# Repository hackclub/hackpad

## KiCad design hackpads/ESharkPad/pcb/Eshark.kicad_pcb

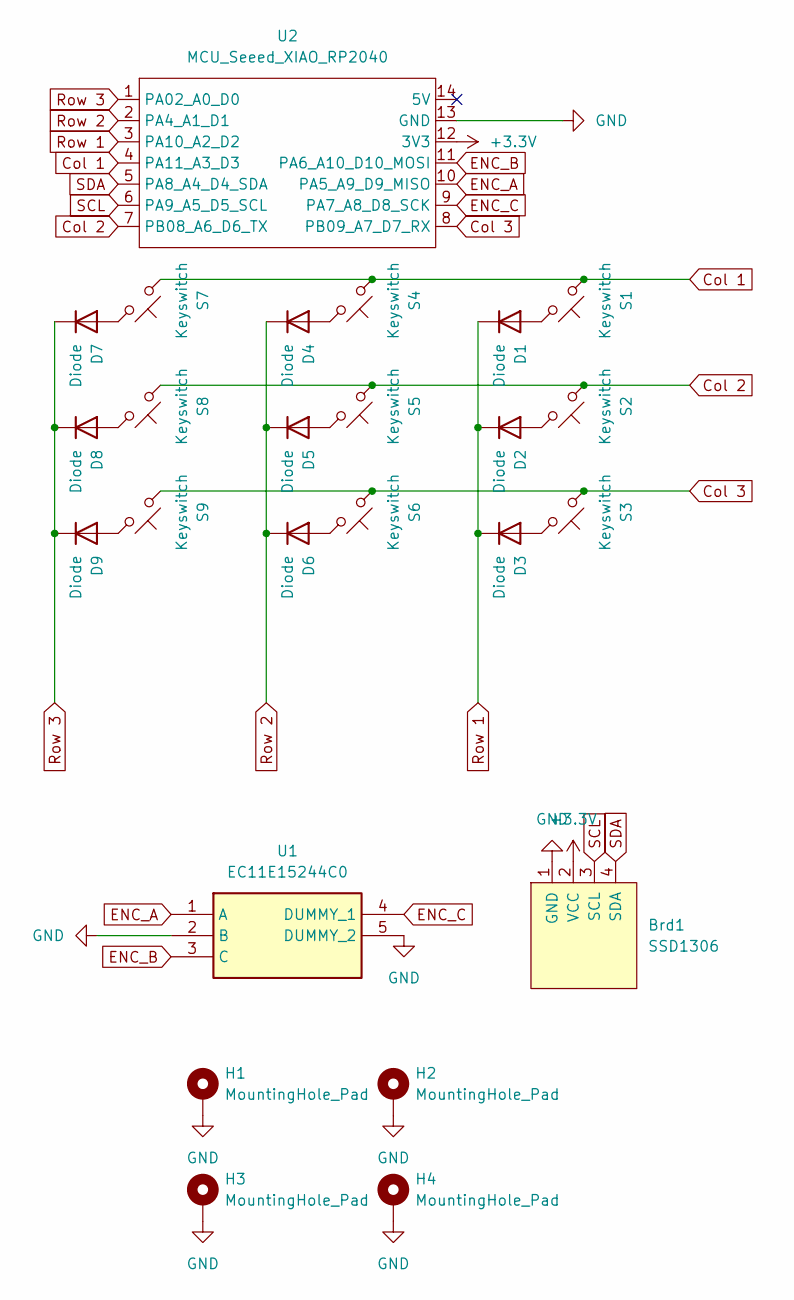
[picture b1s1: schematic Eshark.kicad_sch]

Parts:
Brd1: SSD1306; 128x64OLED
D1, D2, D3, D4, D5, D6, D7, D8, D9: Diode; Diode_DO-35
H1, H2, H3, H4: MountingHole_Pad; MountingHole_2.5mm_Pad_Via
S1, S2, S3, S4, S5, S6, S7, S8, S9: Keyswitch; Kailh-PG1353-Hotswap-1U
U1: EC11E15244C0; EC11B202440M; Manufacturer_Part_Number EC11E15244C0
U2: MCU_Seeed_XIAO_RP2040; Seeed_XIAO_RP2040

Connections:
+3.3V: Brd1.2 (VCC), U2.12 (3V3)
Col 1: S1.1, S4.1, S7.1, U2.4 (PA11_A3_D3)
Col 2: S2.1, S5.1, S8.1, U2.7 (PB08_A6_D6_TX)
Col 3: S3.1, S6.1, S9.1, U2.8 (PB09_A7_D7_RX)
ENC_A: U1.1 (A), U2.10 (PA5_A9_D9_MISO)
ENC_B: U1.3 (C), U2.11 (PA6_A10_D10_MOSI)
ENC_C: U1.4 (DUMMY_1), U2.9 (PA7_A8_D8_SCK)
GND: Brd1.1 (GND), H1.1, H2.1, H3.1, H4.1, U1.2 (B), U1.5 (DUMMY_2), U2.13 (GND)
unnamed: D1.2 (A), S1.2
unnamed: D2.2 (A), S2.2
unnamed: D3.2 (A), S3.2
unnamed: D4.2 (A), S4.2
unnamed: D5.2 (A), S5.2
unnamed: D6.2 (A), S6.2
unnamed: D7.2 (A), S7.2
unnamed: D8.2 (A), S8.2
unnamed: D9.2 (A), S9.2
Row 1: D1.1 (K), D2.1 (K), D3.1 (K), U2.3 (PA10_A2_D2)
Row 2: D4.1 (K), D5.1 (K), D6.1 (K), U2.2 (PA4_A1_D1)
Row 3: D7.1 (K), D8.1 (K), D9.1 (K), U2.1 (PA02_A0_D0)
SCL: Brd1.3 (SCL), U2.6 (PA9_A5_D5_SCL)
SDA: Brd1.4 (SDA), U2.5 (PA8_A4_D4_SDA)

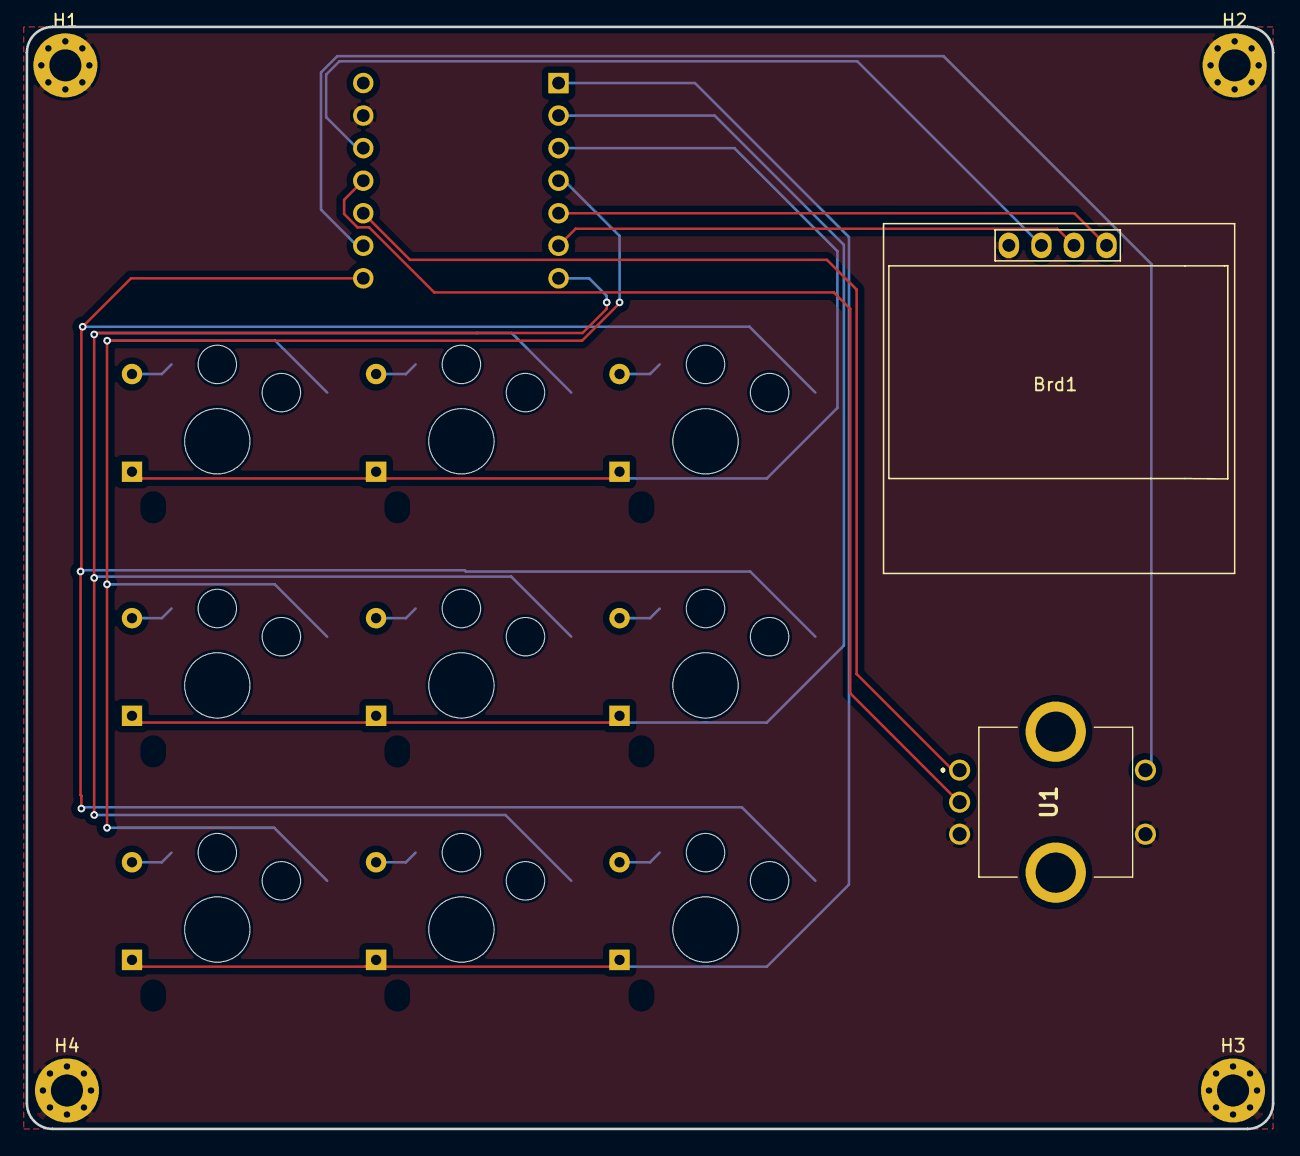
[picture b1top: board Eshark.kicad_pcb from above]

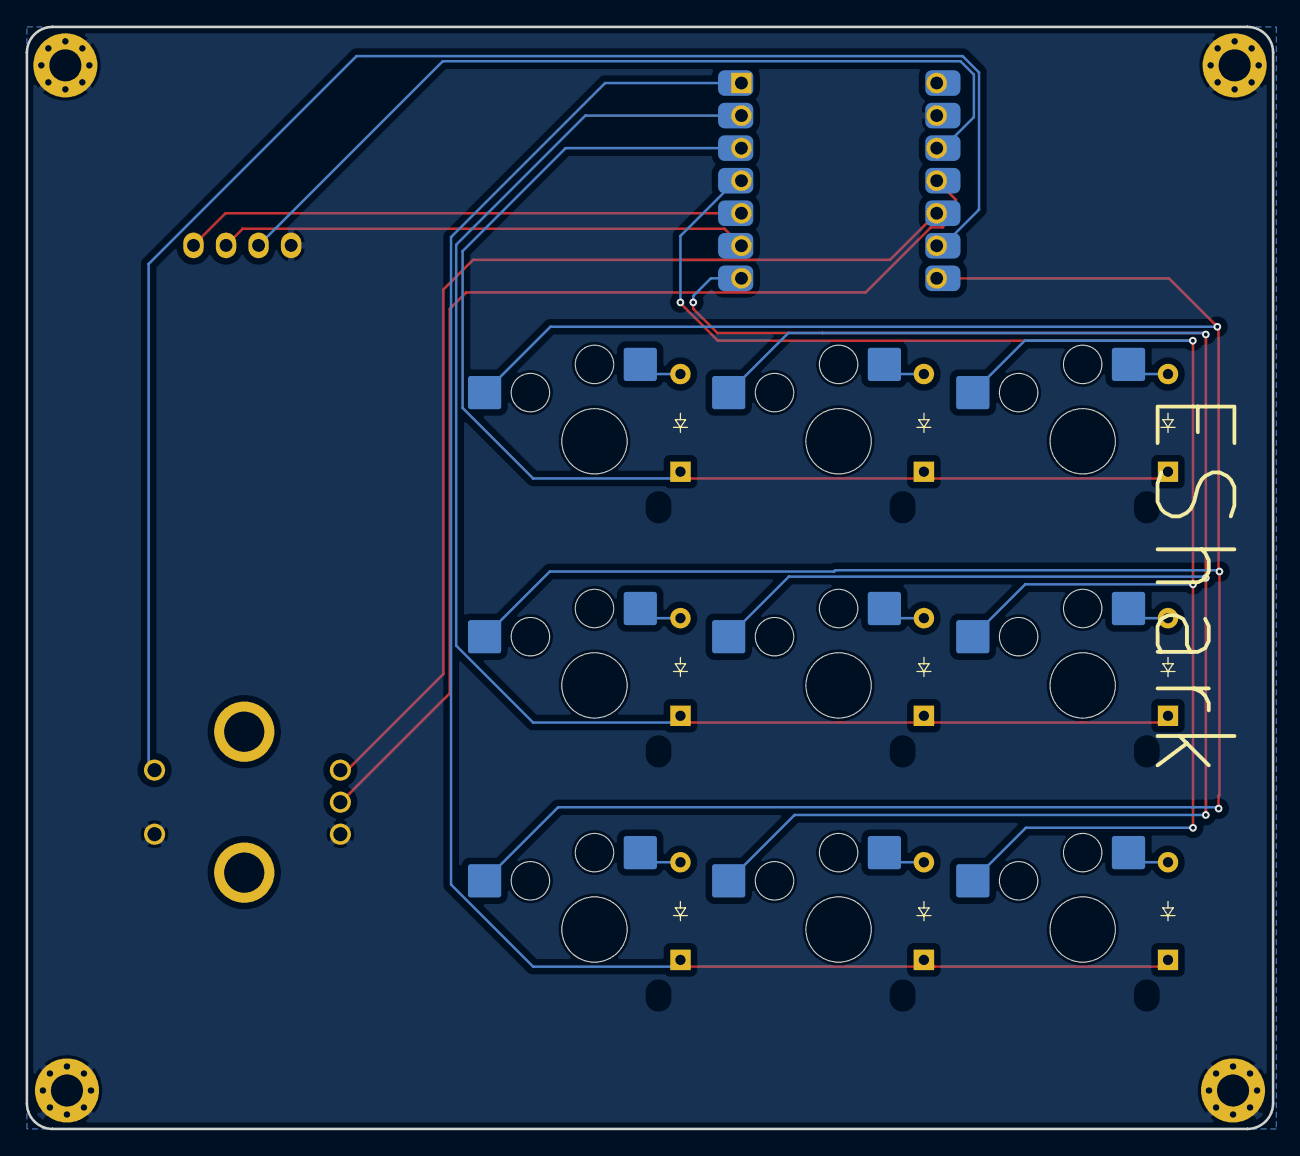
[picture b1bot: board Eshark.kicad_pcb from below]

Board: 2 copper layers, 97.2 x 86.0 mm, 25 parts (19 on the bottom side), 22 nets.

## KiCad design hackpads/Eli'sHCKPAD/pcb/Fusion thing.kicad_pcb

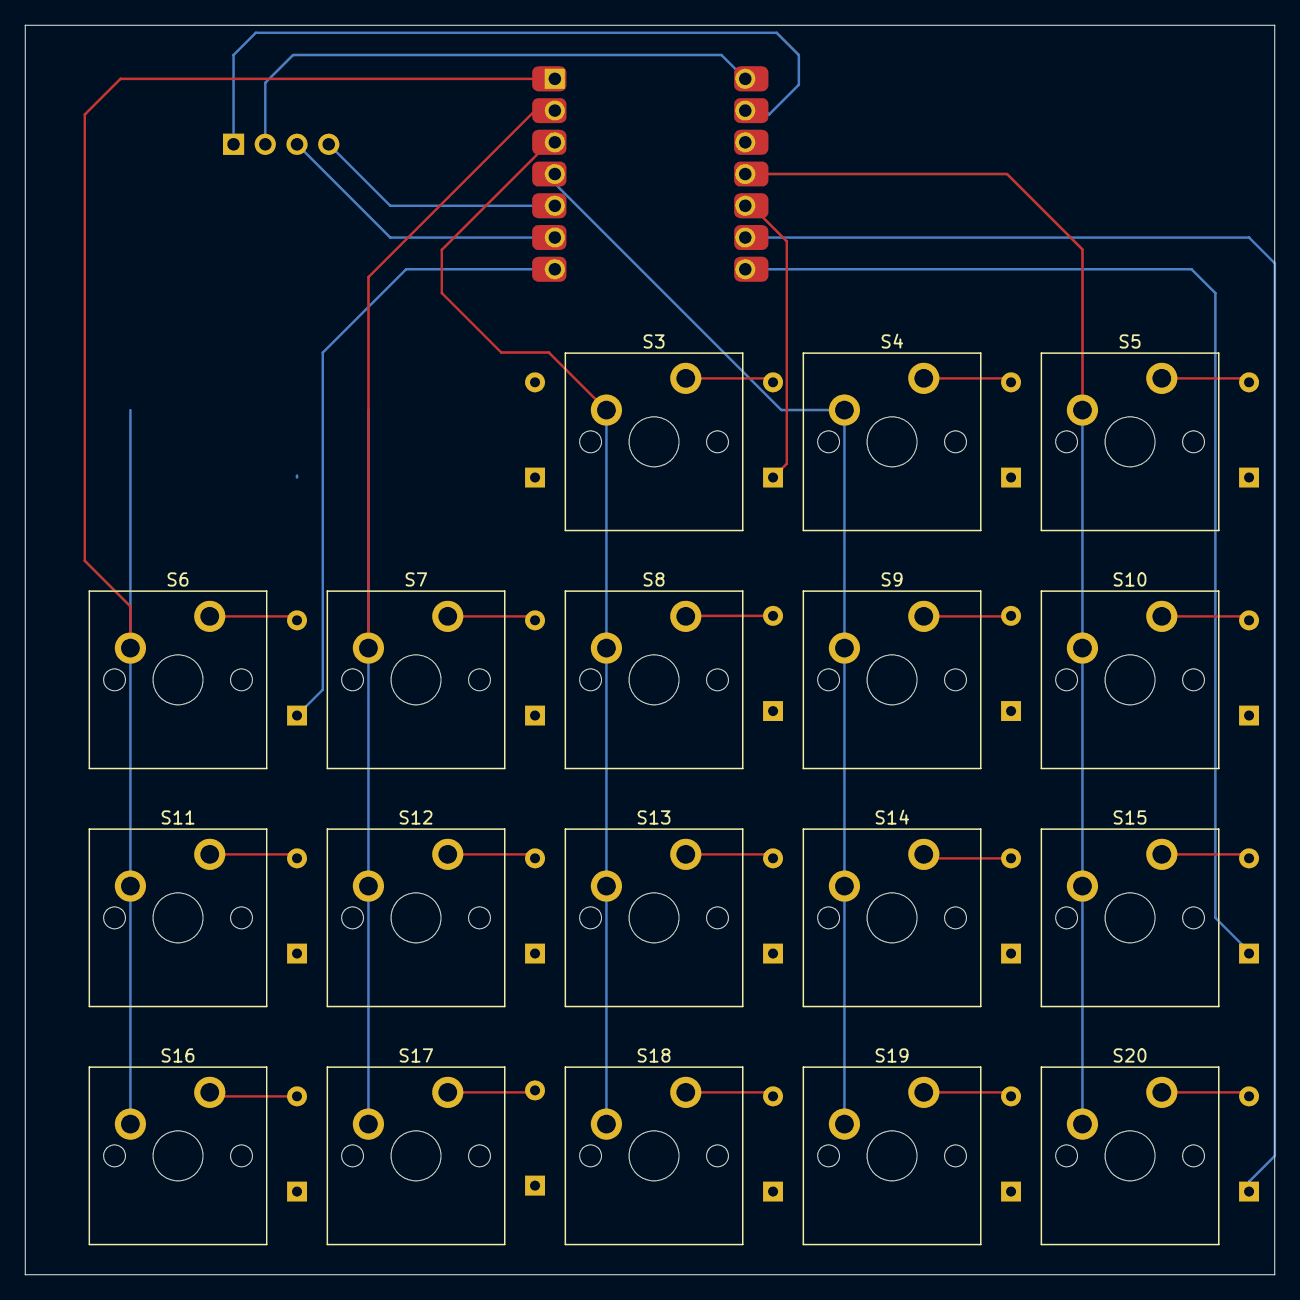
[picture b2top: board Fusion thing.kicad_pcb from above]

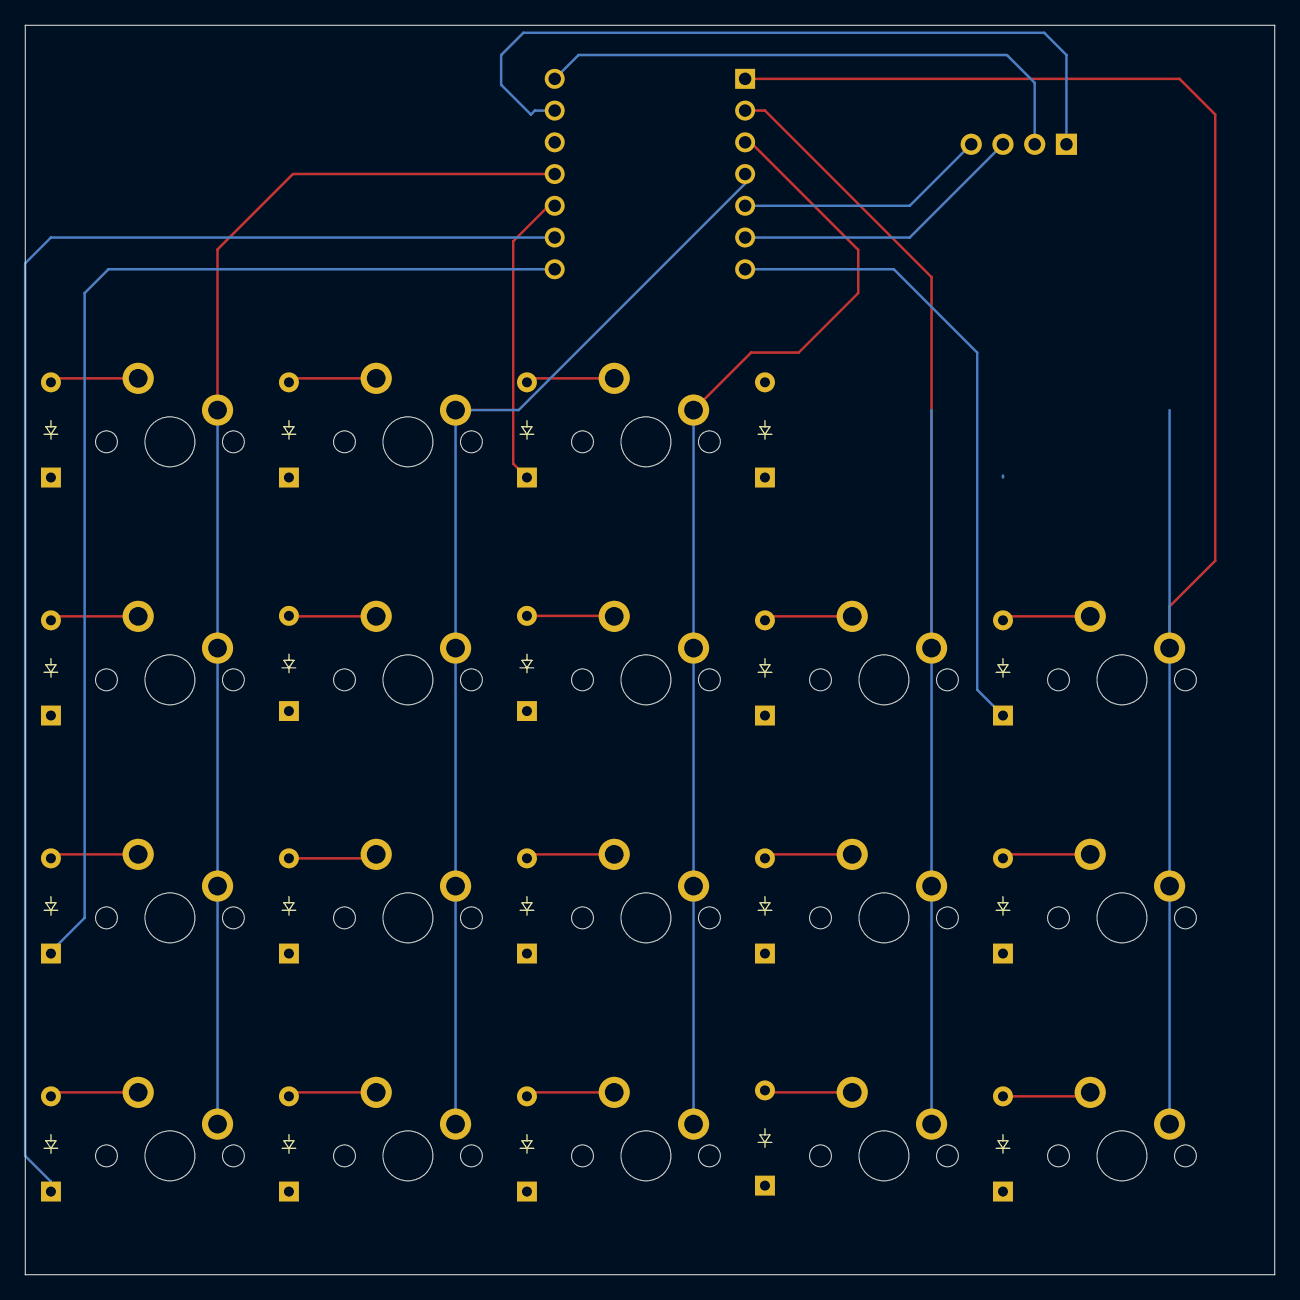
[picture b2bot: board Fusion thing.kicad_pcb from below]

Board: 2 copper layers, 100.0 x 100.0 mm, 39 parts (19 on the bottom side), 31 nets.

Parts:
D2, D3, D4, D5, D6, D7, D8, D9, D10, D11, D12, D13, D14, D15, D16, D17, D18, D19, D20: Diode; Diode_DO-35
J1: OLED_128x64
S3, S4, S5, S6, S7, S8, S9, S10, S11, S12, S13, S14, S15, S16, S17, S18, S19, S20: Keyswitch; MX_PCB_1.00u
U1: MCU_Seeed_XIAO_RP2040; Seeed_XIAO_RP2040

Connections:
Gnd: J1.1 (GND), U1.13 (GND)
unnamed: D3.2 (A), S3.2
unnamed: D4.2 (A), S4.2
unnamed: D5.2 (A), S5.2
unnamed: D6.2 (A), S6.2
unnamed: D7.2 (A), S7.2
unnamed: D8.2 (A), S8.2
unnamed: D9.2 (A), S9.2
unnamed: D10.2 (A), S10.2
unnamed: D11.2 (A), S11.2
unnamed: D12.2 (A), S12.2
unnamed: D13.2 (A), S13.2
unnamed: D14.2 (A), S14.2
unnamed: D15.2 (A), S15.2
unnamed: D16.2 (A), S16.2
unnamed: D17.2 (A), S17.2
unnamed: D18.2 (A), S18.2
unnamed: D19.2 (A), S19.2
unnamed: D20.2 (A), S20.2
SCL: J1.3 (SCL), U1.6 (PA9_A5_D5_SCL)
SDA: J1.4 (SDA), U1.5 (PA8_A4_D4_SDA)
VCC: J1.2 (VCC), U1.14 (5V)
column1: S6.1, S11.1, S16.1, U1.1 (PA02_A0_D0)
column2: S7.1, S12.1, S17.1, U1.2 (PA4_A1_D1)
column3: S3.1, S8.1, S13.1, S18.1, U1.3 (PA10_A2_D2)
column4: S4.1, S9.1, S14.1, S19.1, U1.4 (PA11_A3_D3)
column5: S5.1, S10.1, S15.1, S20.1, U1.11 (PA6_A10_D10_MOSI)
row1: D2.1 (K), D3.1 (K), D4.1 (K), D5.1 (K), U1.10 (PA5_A9_D9_MISO)
row2: D6.1 (K), D7.1 (K), D8.1 (K), D9.1 (K), D10.1 (K), U1.7 (PB08_A6_D6_TX)
row3: D11.1 (K), D12.1 (K), D13.1 (K), D14.1 (K), D15.1 (K), U1.8 (PB09_A7_D7_RX)
row4: D16.1 (K), D17.1 (K), D18.1 (K), D19.1 (K), D20.1 (K), U1.9 (PA7_A8_D8_SCK)

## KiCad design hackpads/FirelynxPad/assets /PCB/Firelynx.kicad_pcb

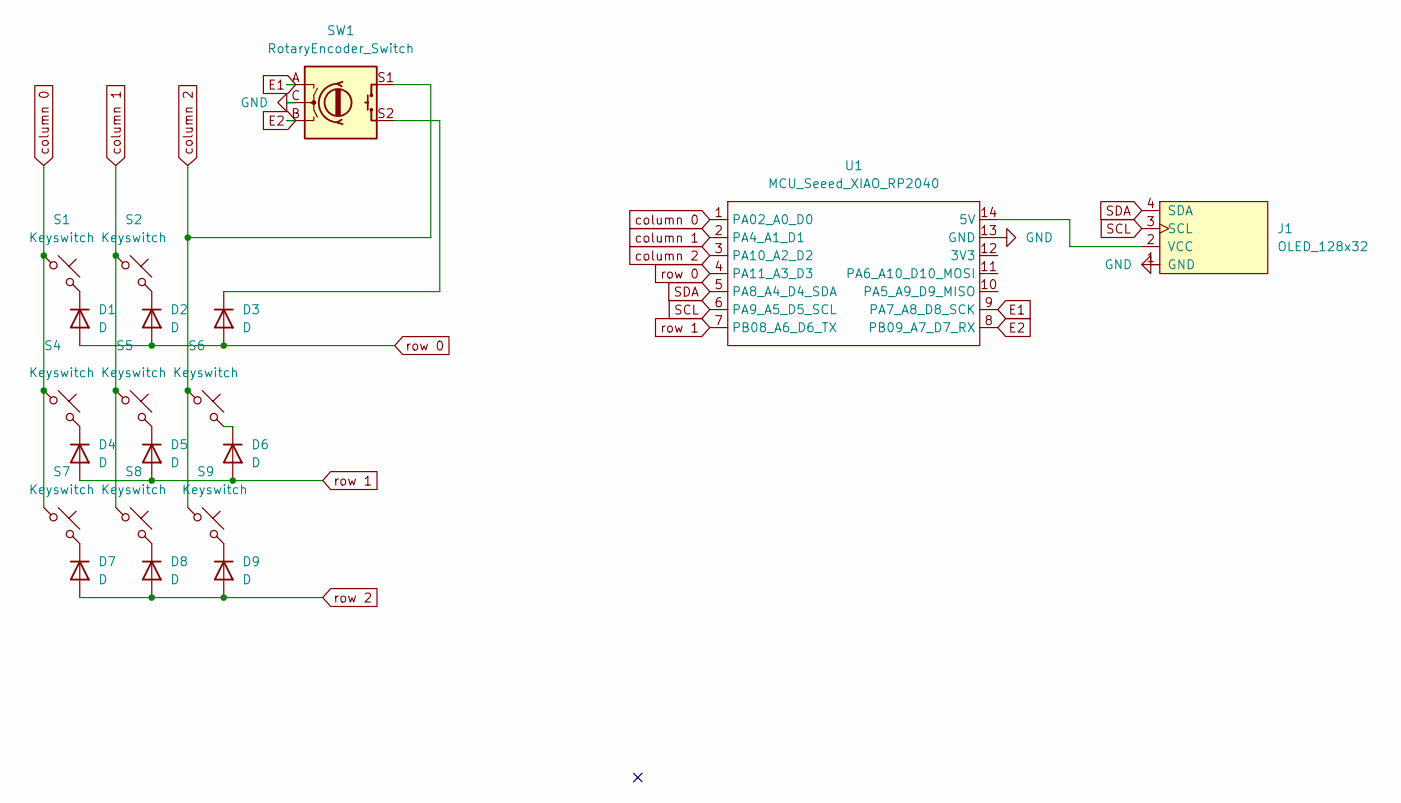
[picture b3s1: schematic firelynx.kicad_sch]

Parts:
D1, D2, D3, D4, D5, D6, D7, D8, D9: D; D_DO-35_SOD27_P7.62mm_Horizontal
J1: OLED_128x32
S1, S2, S4, S5, S6, S7, S8, S9: Keyswitch; SW_Cherry_MX_1.00u_PCB
SW1: RotaryEncoder_Switch; RotaryEncoder_Alps_EC11E-Switch_Vertical_H20mm
U1: MCU_Seeed_XIAO_RP2040; Seeed_XIAO_RP2040

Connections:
E1: SW1.A, U1.9 (PA7_A8_D8_SCK)
E2: SW1.B, U1.8 (PB09_A7_D7_RX)
GND: SW1.C, U1.13 (GND)
unnamed: D1.1 (K), S1.2
unnamed: D2.1 (K), S2.2
unnamed: D3.1 (K), SW1.S2
unnamed: D4.1 (K), S4.2
unnamed: D5.1 (K), S5.2
unnamed: D6.1 (K), S6.2
unnamed: D7.1 (K), S7.2
unnamed: D8.1 (K), S8.2
unnamed: D9.1 (K), S9.2
unnamed: J1.2 (VCC), U1.14 (5V)
SCL: J1.3 (SCL), U1.6 (PA9_A5_D5_SCL)
SDA: J1.4 (SDA), U1.5 (PA8_A4_D4_SDA)
column 0: S1.1, S4.1, S7.1, U1.1 (PA02_A0_D0)
column 1: S2.1, S5.1, S8.1, U1.2 (PA4_A1_D1)
column 2: S6.1, S9.1, SW1.S1, U1.3 (PA10_A2_D2)
row 0: D1.2 (A), D2.2 (A), D3.2 (A), U1.4 (PA11_A3_D3)
row 1: D4.2 (A), D5.2 (A), D6.2 (A), U1.7 (PB08_A6_D6_TX)
row 2: D7.2 (A), D8.2 (A), D9.2 (A)

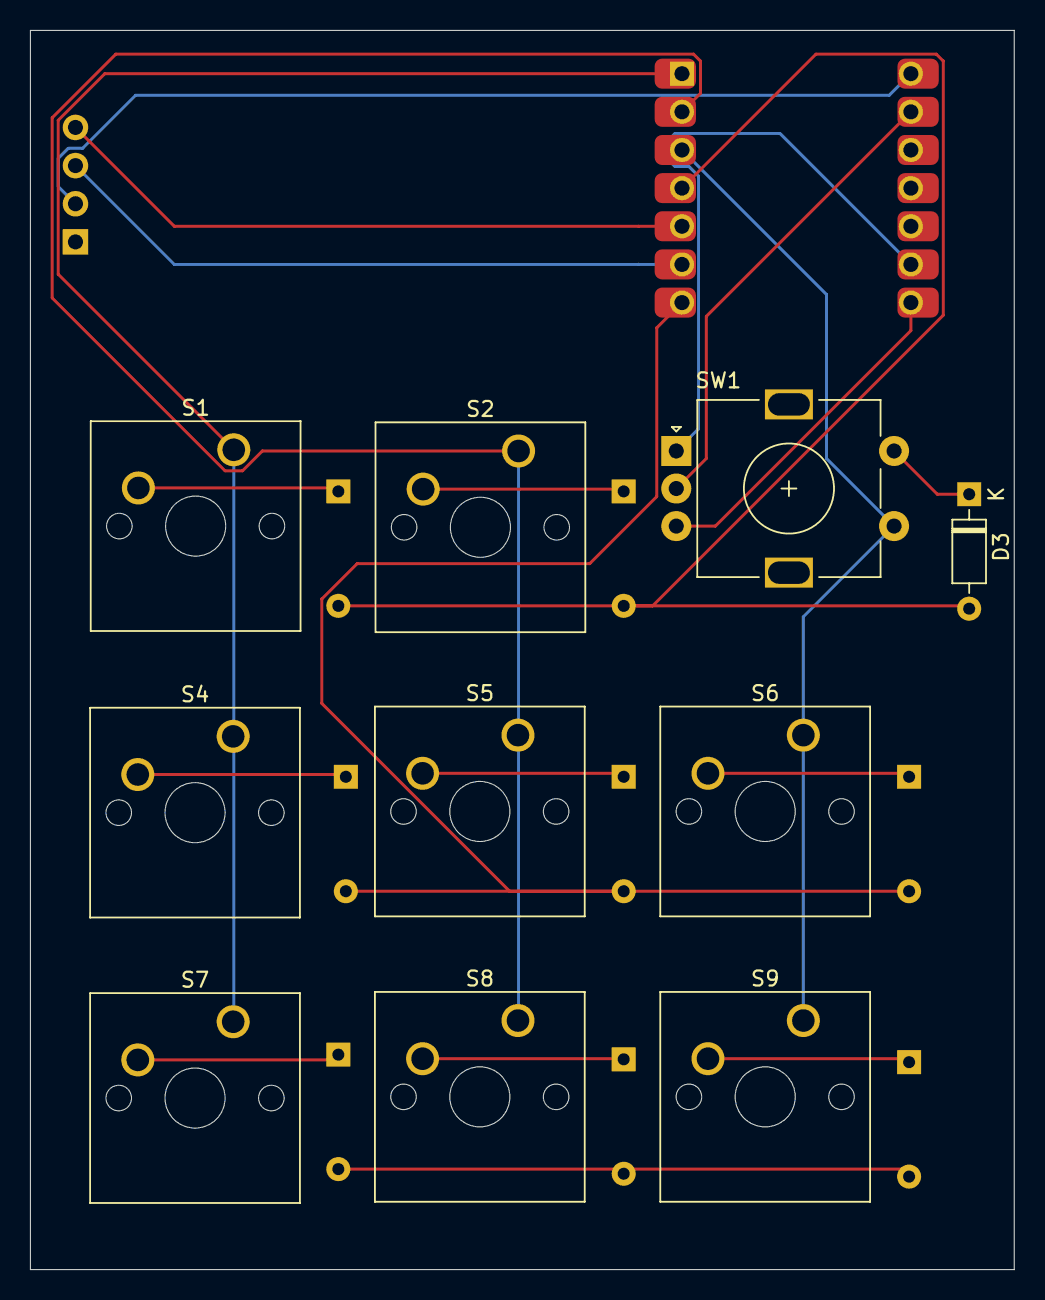
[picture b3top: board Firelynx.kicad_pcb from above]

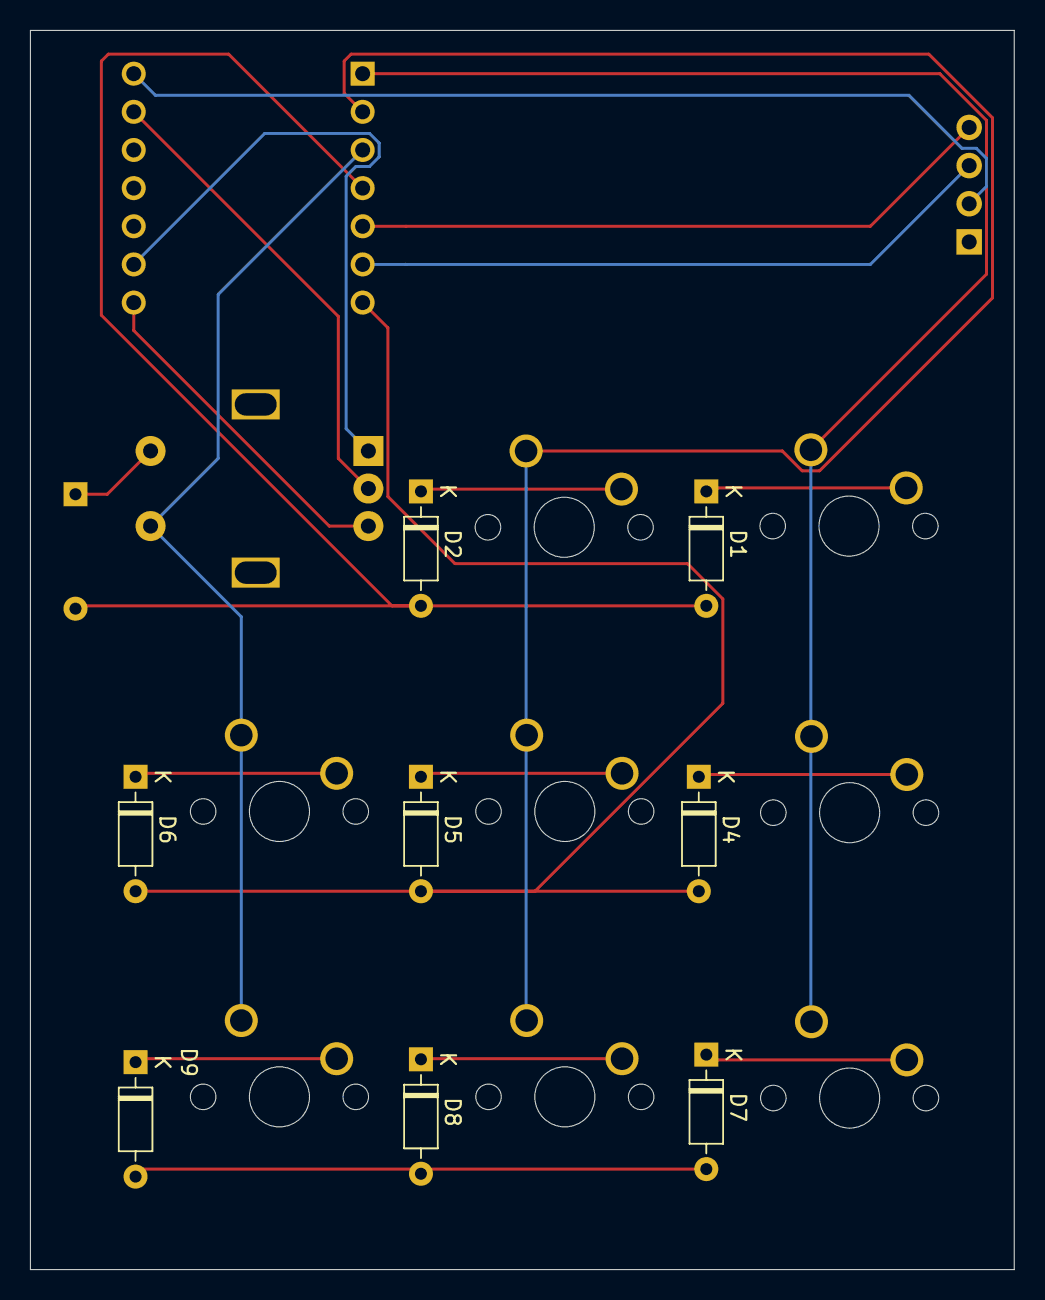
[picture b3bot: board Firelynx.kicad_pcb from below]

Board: 2 copper layers, 65.5 x 82.5 mm, 20 parts (8 on the bottom side), 21 nets.

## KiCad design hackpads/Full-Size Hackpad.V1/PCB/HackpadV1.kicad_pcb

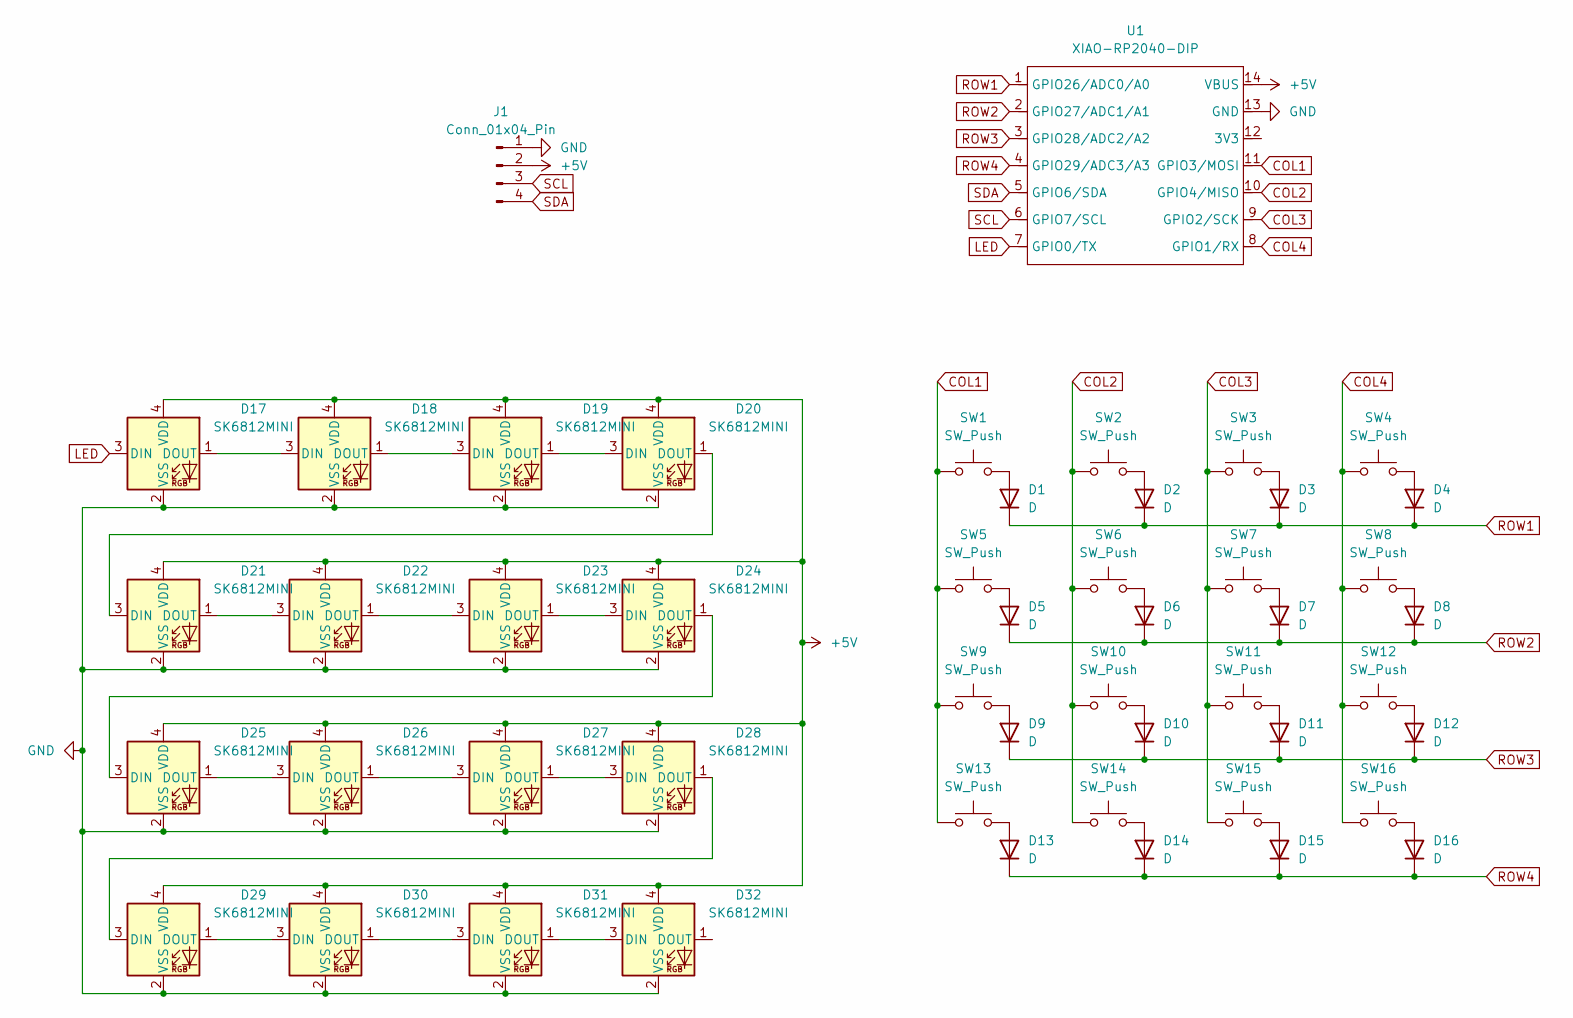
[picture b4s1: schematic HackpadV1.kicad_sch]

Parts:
D1, D2, D3, D4, D5, D6, D7, D8, D9, D10, D11, D12, D13, D14, D15, D16: D; D_DO-35_SOD27_P7.62mm_Horizontal
D17, D18, D19, D20, D21, D22, D23, D24, D25, D26, D27, D28, D29, D30, D31, D32: SK6812MINI; SK6812MINI-E
J1: Conn_01x04_Pin; SSD1306-0.91-OLED-4pin-128x32
SW1, SW2, SW3, SW4, SW5, SW6, SW7, SW8, SW9, SW10, SW11, SW12, SW13, SW14, SW15, SW16: SW_Push; SW_Cherry_MX_1.00u_PCB
U1: XIAO-RP2040-DIP

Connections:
+5V: D17.4 (VDD), D18.4 (VDD), D19.4 (VDD), D20.4 (VDD), D21.4 (VDD), D22.4 (VDD), D23.4 (VDD), D24.4 (VDD), D25.4 (VDD), D26.4 (VDD), D27.4 (VDD), D28.4 (VDD), D29.4 (VDD), D30.4 (VDD), D31.4 (VDD), D32.4 (VDD), J1.2, U1.14 (VBUS)
COL1: SW1.1, SW5.1, SW9.1, SW13.1, U1.11 (GPIO3/MOSI)
COL2: SW2.1, SW6.1, SW10.1, SW14.1, U1.10 (GPIO4/MISO)
COL3: SW3.1, SW7.1, SW11.1, SW15.1, U1.9 (GPIO2/SCK)
COL4: SW4.1, SW8.1, SW12.1, SW16.1, U1.8 (GPIO1/RX)
GND: D17.2 (VSS), D18.2 (VSS), D19.2 (VSS), D20.2 (VSS), D21.2 (VSS), D22.2 (VSS), D23.2 (VSS), D24.2 (VSS), D25.2 (VSS), D26.2 (VSS), D27.2 (VSS), D28.2 (VSS), D29.2 (VSS), D30.2 (VSS), D31.2 (VSS), D32.2 (VSS), J1.1, U1.13 (GND)
LED: D17.3 (DIN), U1.7 (GPIO0/TX)
unnamed: D1.2 (A), SW1.2
unnamed: D2.2 (A), SW2.2
unnamed: D3.2 (A), SW3.2
unnamed: D4.2 (A), SW4.2
unnamed: D5.2 (A), SW5.2
unnamed: D6.2 (A), SW6.2
unnamed: D7.2 (A), SW7.2
unnamed: D8.2 (A), SW8.2
unnamed: D9.2 (A), SW9.2
unnamed: D10.2 (A), SW10.2
unnamed: D11.2 (A), SW11.2
unnamed: D12.2 (A), SW12.2
unnamed: D13.2 (A), SW13.2
unnamed: D14.2 (A), SW14.2
unnamed: D15.2 (A), SW15.2
unnamed: D16.2 (A), SW16.2
unnamed: D17.1 (DOUT), D18.3 (DIN)
unnamed: D18.1 (DOUT), D19.3 (DIN)
unnamed: D19.1 (DOUT), D20.3 (DIN)
unnamed: D20.1 (DOUT), D21.3 (DIN)
unnamed: D21.1 (DOUT), D22.3 (DIN)
unnamed: D22.1 (DOUT), D23.3 (DIN)
unnamed: D23.1 (DOUT), D24.3 (DIN)
unnamed: D24.1 (DOUT), D25.3 (DIN)
unnamed: D25.1 (DOUT), D26.3 (DIN)
unnamed: D26.1 (DOUT), D27.3 (DIN)
unnamed: D27.1 (DOUT), D28.3 (DIN)
unnamed: D28.1 (DOUT), D29.3 (DIN)
unnamed: D29.1 (DOUT), D30.3 (DIN)
unnamed: D30.1 (DOUT), D31.3 (DIN)
unnamed: D31.1 (DOUT), D32.3 (DIN)
ROW1: D1.1 (K), D2.1 (K), D3.1 (K), D4.1 (K), U1.1 (GPIO26/ADC0/A0)
ROW2: D5.1 (K), D6.1 (K), D7.1 (K), D8.1 (K), U1.2 (GPIO27/ADC1/A1)
ROW3: D9.1 (K), D10.1 (K), D11.1 (K), D12.1 (K), U1.3 (GPIO28/ADC2/A2)
ROW4: D13.1 (K), D14.1 (K), D15.1 (K), D16.1 (K), U1.4 (GPIO29/ADC3/A3)
SCL: J1.3, U1.6 (GPIO7/SCL)
SDA: J1.4, U1.5 (GPIO6/SDA)

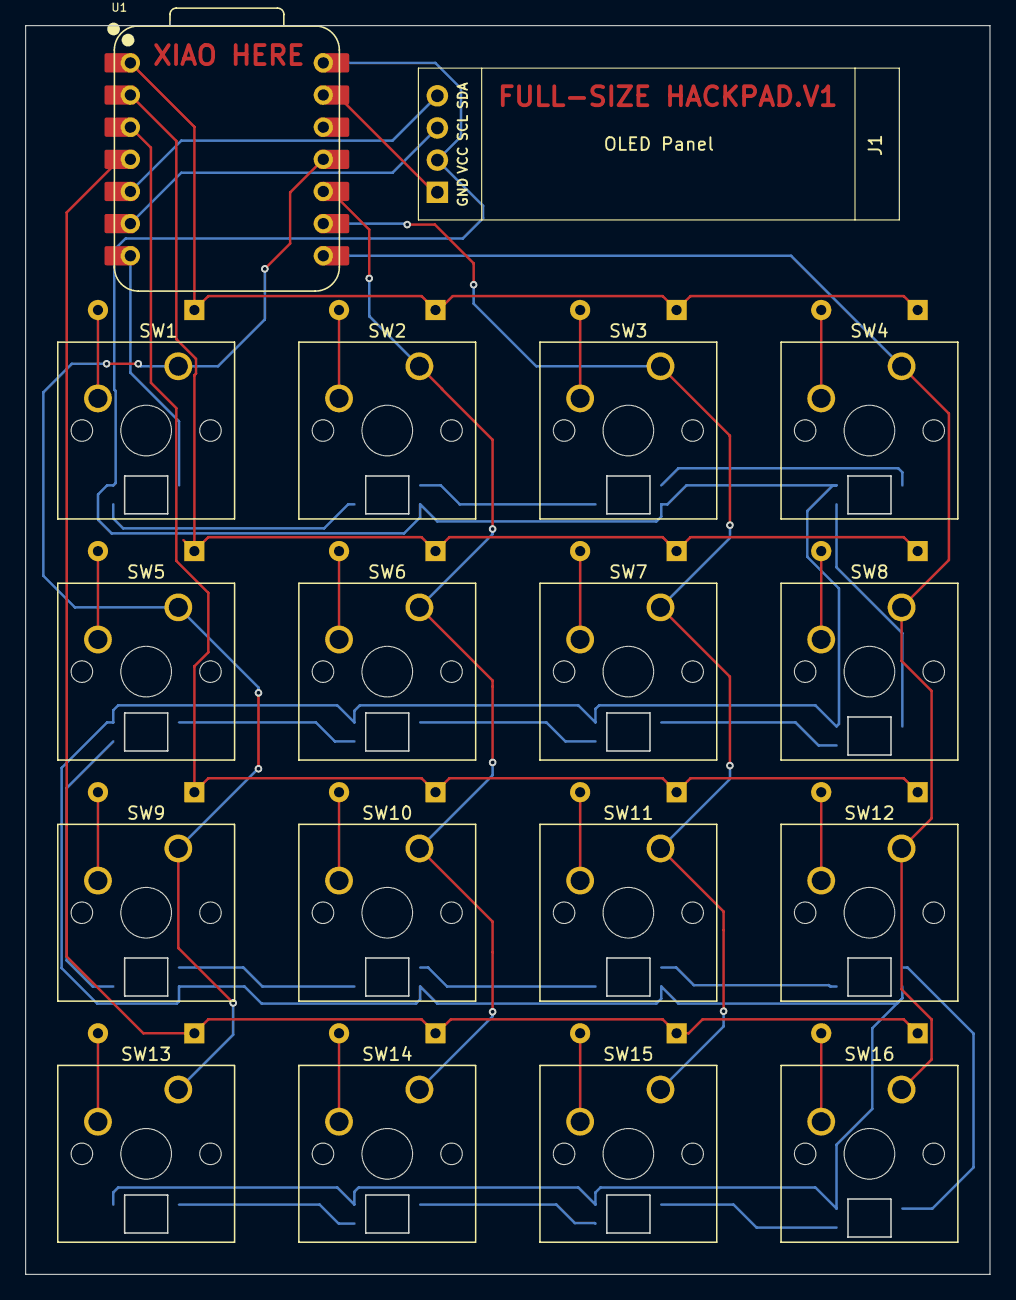
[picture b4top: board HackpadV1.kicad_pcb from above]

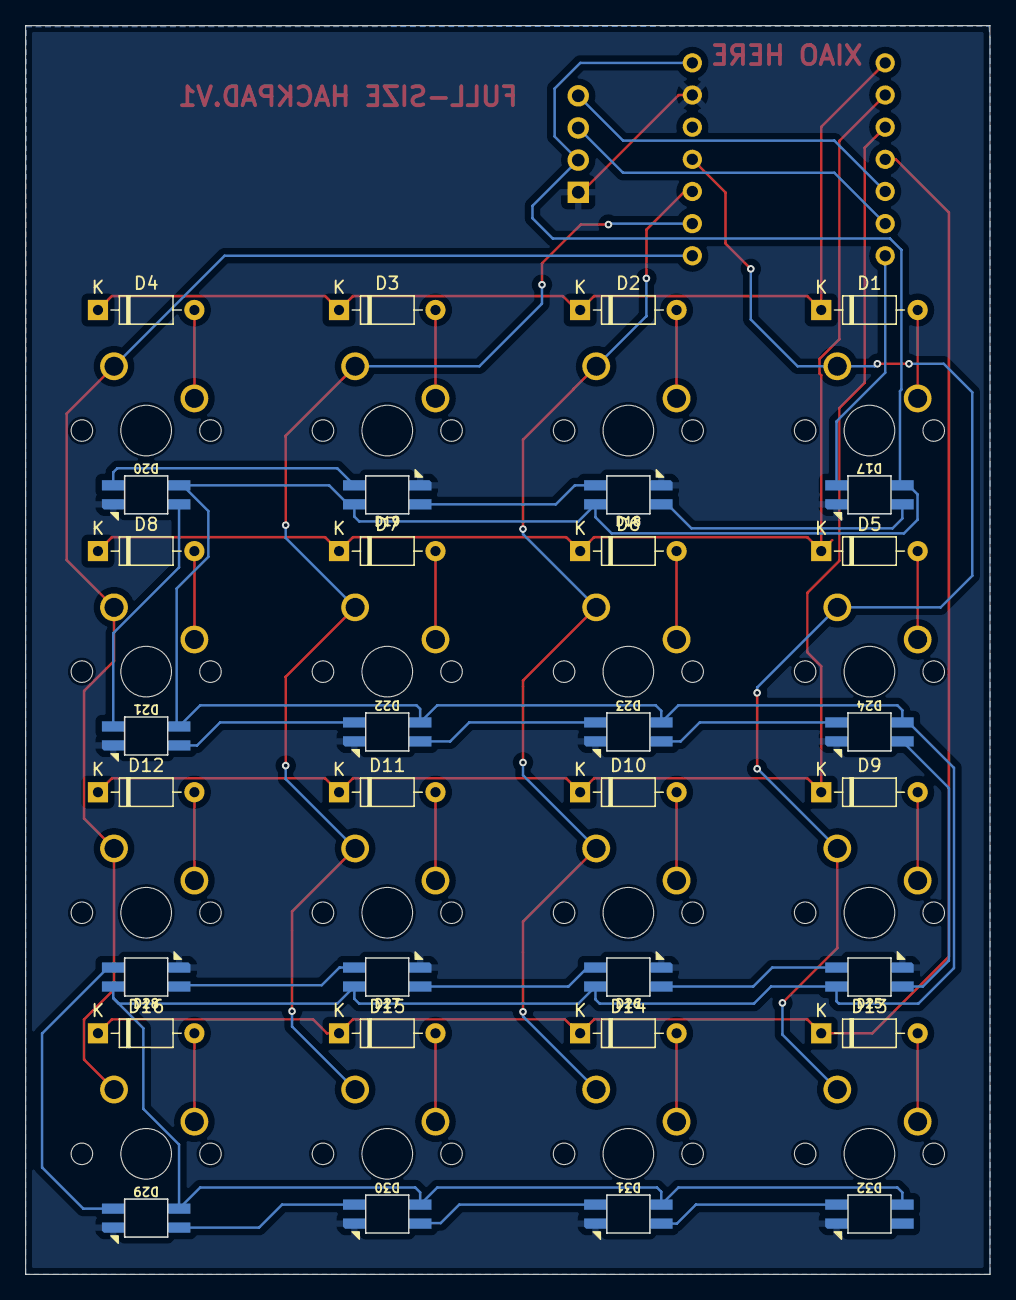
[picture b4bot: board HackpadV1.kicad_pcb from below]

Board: 2 copper layers, 76.2 x 98.7 mm, 50 parts (32 on the bottom side), 44 nets.

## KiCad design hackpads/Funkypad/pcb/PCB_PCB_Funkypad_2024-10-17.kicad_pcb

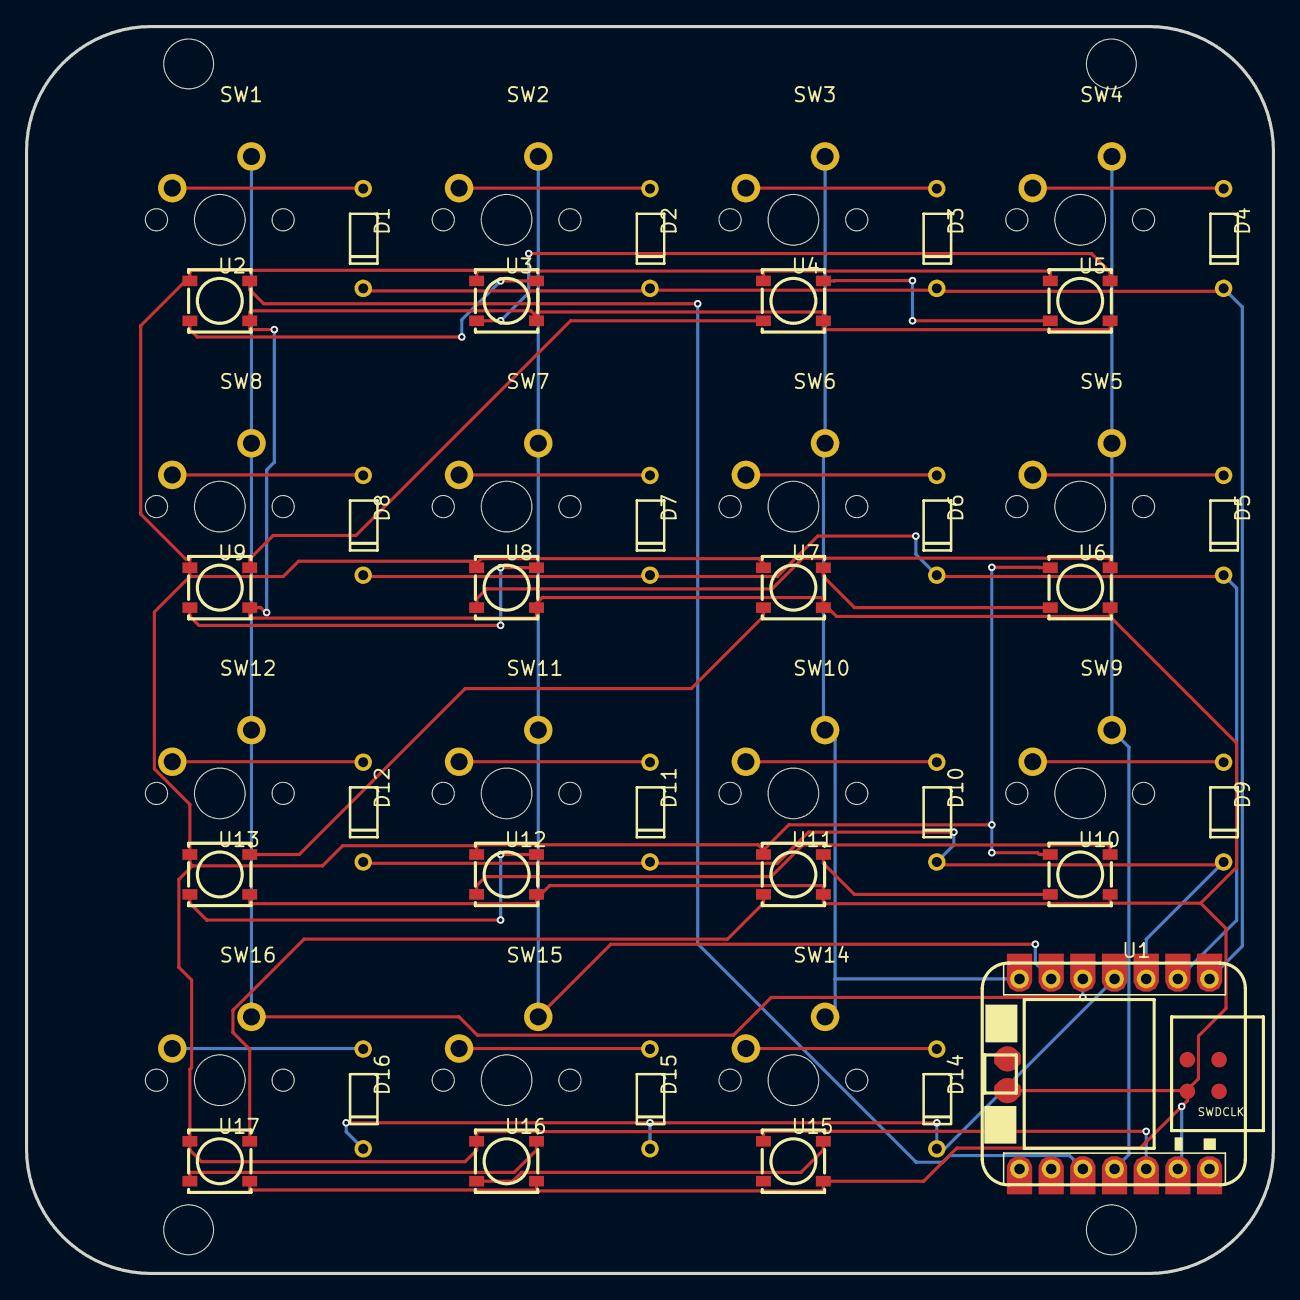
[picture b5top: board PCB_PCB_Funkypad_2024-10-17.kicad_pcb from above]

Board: 2 copper layers, 100.0 x 100.0 mm, 46 parts (0 on the bottom side), 40 nets.

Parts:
D1, D2, D3, D4, D5, D6, D7, D8, D9, D10, D11, D12, D14, D15, D16: 1N4148_C18195411; DO-35_BD2.2-L4.0-D0.50_1N4148
SW1, SW2, SW3, SW4, SW5, SW6, SW7, SW8, SW9, SW10, SW11, SW12, SW14, SW15, SW16: CHERRY MX SWITCH 1.0U
U1: SEEED XIAO RP2040; XIAO RP2040 V1.22_BOARD
U2, U3, U4, U5, U6, U7, U8, U9, U10, U11, U12, U13, U15, U16, U17: 5050WS2812B; LED-SMD_5050WS2812B

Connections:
COL0: SW1.C, SW8.C, SW12.C, SW16.C, U1.4
COL1: SW2.C, SW7.C, SW11.C, SW15.C, U1.5
COL2: SW3.C, SW6.C, SW10.C, SW14.C, U1.6
COL3: SW4.C, SW5.C, SW9.C, U1.10
D2_1: D2.1, SW2.R
D3_1: D3.1, SW3.R
D4_1: D4.1, SW4.R
D8_1: D8.1, SW8.R
D12_1: D12.1, SW12.R
D16_1: D16.1, SW16.R
DIN: U1.9, U2.4
GND: U1.GND, U2.3, U3.3, U4.3, U5.3, U6.3, U7.3, U8.3, U9.3, U10.3, U11.3, U12.3, U13.3, U15.3, U16.3, U17.3
ROW0: D1.2, D2.2, D3.2, D4.2, U1.0
ROW1: D5.2, D6.2, D7.2, D8.2, U1.1
ROW2: D9.2, D10.2, D11.2, D12.2, U1.2
ROW3: D14.2, D15.2, D16.2, U1.3
SW1_R: D1.1, SW1.R
SW5_R: D5.1, SW5.R
SW6_R: D6.1, SW6.R
SW7_R: D7.1, SW7.R
SW9_R: D9.1, SW9.R
SW10_R: D10.1, SW10.R
SW11_R: D11.1, SW11.R
SW14_R: D14.1, SW14.R
SW15_R: D15.1, SW15.R
U2_2: U2.2, U3.4
U3_2: U3.2, U5.4
U4_2: U4.2, U9.4
U4_4: U4.4, U5.2
U6_2: U6.2, U7.4
U6_4: U6.4, U8.2
U7_2: U7.2, U13.4
U8_4: U8.4, U9.2
U10_2: U10.2, U11.4
U10_4: U10.4, U12.2
U11_2: U11.2, U17.4
U12_4: U12.4, U13.2
U15_4: U15.4, U16.2
U16_4: U16.4, U17.2
VCC: U1.3, U2.1, U3.1, U4.1, U5.1, U6.1, U7.1, U8.1, U9.1, U10.1, U11.1, U12.1, U13.1, U15.1, U16.1, U17.1
